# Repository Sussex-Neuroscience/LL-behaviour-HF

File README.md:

# LL-behaviour-HF

a behavioural control system for head fixed mice

The task:

- At the start there is a 10 sec interval without a stimulus to record baseline activity. Then the mouse sees a stimulus (always the same drifting grating) which appears randomly either on the left or the right screen. after 5 sec. of stimulus presentation the actuator moves the lick sensors in front of the mouse for two sec. in which the mouse has to report on which side the stimulus is present, hence lick left or right. If the answer is correct a reward is given (solenoid valves). If the answer is incorrect no reward is given. The actuator retracts the lick sensors after 2 sec. either way. Then there is an inter trial interval for 5+ sec before the next stimulus will be presented. If the mouse was incorrect the stimulus will be presented on the same side as the trial before until the mouse makes the correct decision (to avoid bias).I might want to change the timeframes for the different stages depending on how the training goes.

- There will also be a second task where stimuli are presented on both sides on the screen (differing in orientation or contrast) and the animal has to decide which of the stimuli is the correct one. The time course will be the same, it is just the task that is changing.

- The stimulus orientation, size, contrast, frequencies etc. will be different for every mouse but will be the same throughout the training sessions, so there is only 1 type of stimulus in the first task and 2 type of stimuli in the second task. 

- The random stimulus presentation isn't in the code yet. So far, there was no task for the animal, so we always displayed the same stimulus on both sides simultaneously by mirroring one screen to the other. I'll have another chat with Antonio today to see how trivial it is to change that towards what I need.

- As for the scanimage channels. Yes, I was talking about the analog inputs. The DAQ has a lot of free slots left and I guess there are free digital inputs. I'm not too familiar with setting these things up.

- If everything works just using the labjack that would be great. We have an Arduino uno lying around just in case it is needed.

---

schematics on how the system is working and how it should work:

--- 

### notes on implementation:

from what I could gather, Psychopy is not indicated to do millisecond precision of many different variables at once. I had a look on how it deals with timing (more info [here](https://www.psychopy.org/_modules/psychopy/clock.html#Clock)), and thinking that a good route would be to do the behavioural timing critical things on the ESP32.

---

initial bill of materials:

|||
|---|---|
|Linear actuator||
|solenoid valves||
|lick sensors||
|beehive main board||
|beehive peltier board||
|beehive solenoid valve board||
|||

---

software needed to run the esp32
REPL
esp32 micropython firmware
adafruit Ampy

---

notes from the first installation session:

- the Optogenetics LED is controlled by a Thorlabs DC2200 interface. It gets its signals from an arduino box, which in principle can be bypassed since we are already using a microcontroller to take care of the behavioural task.
- from labjack to scanimage there are 2 signals timewave and twoptrigger.

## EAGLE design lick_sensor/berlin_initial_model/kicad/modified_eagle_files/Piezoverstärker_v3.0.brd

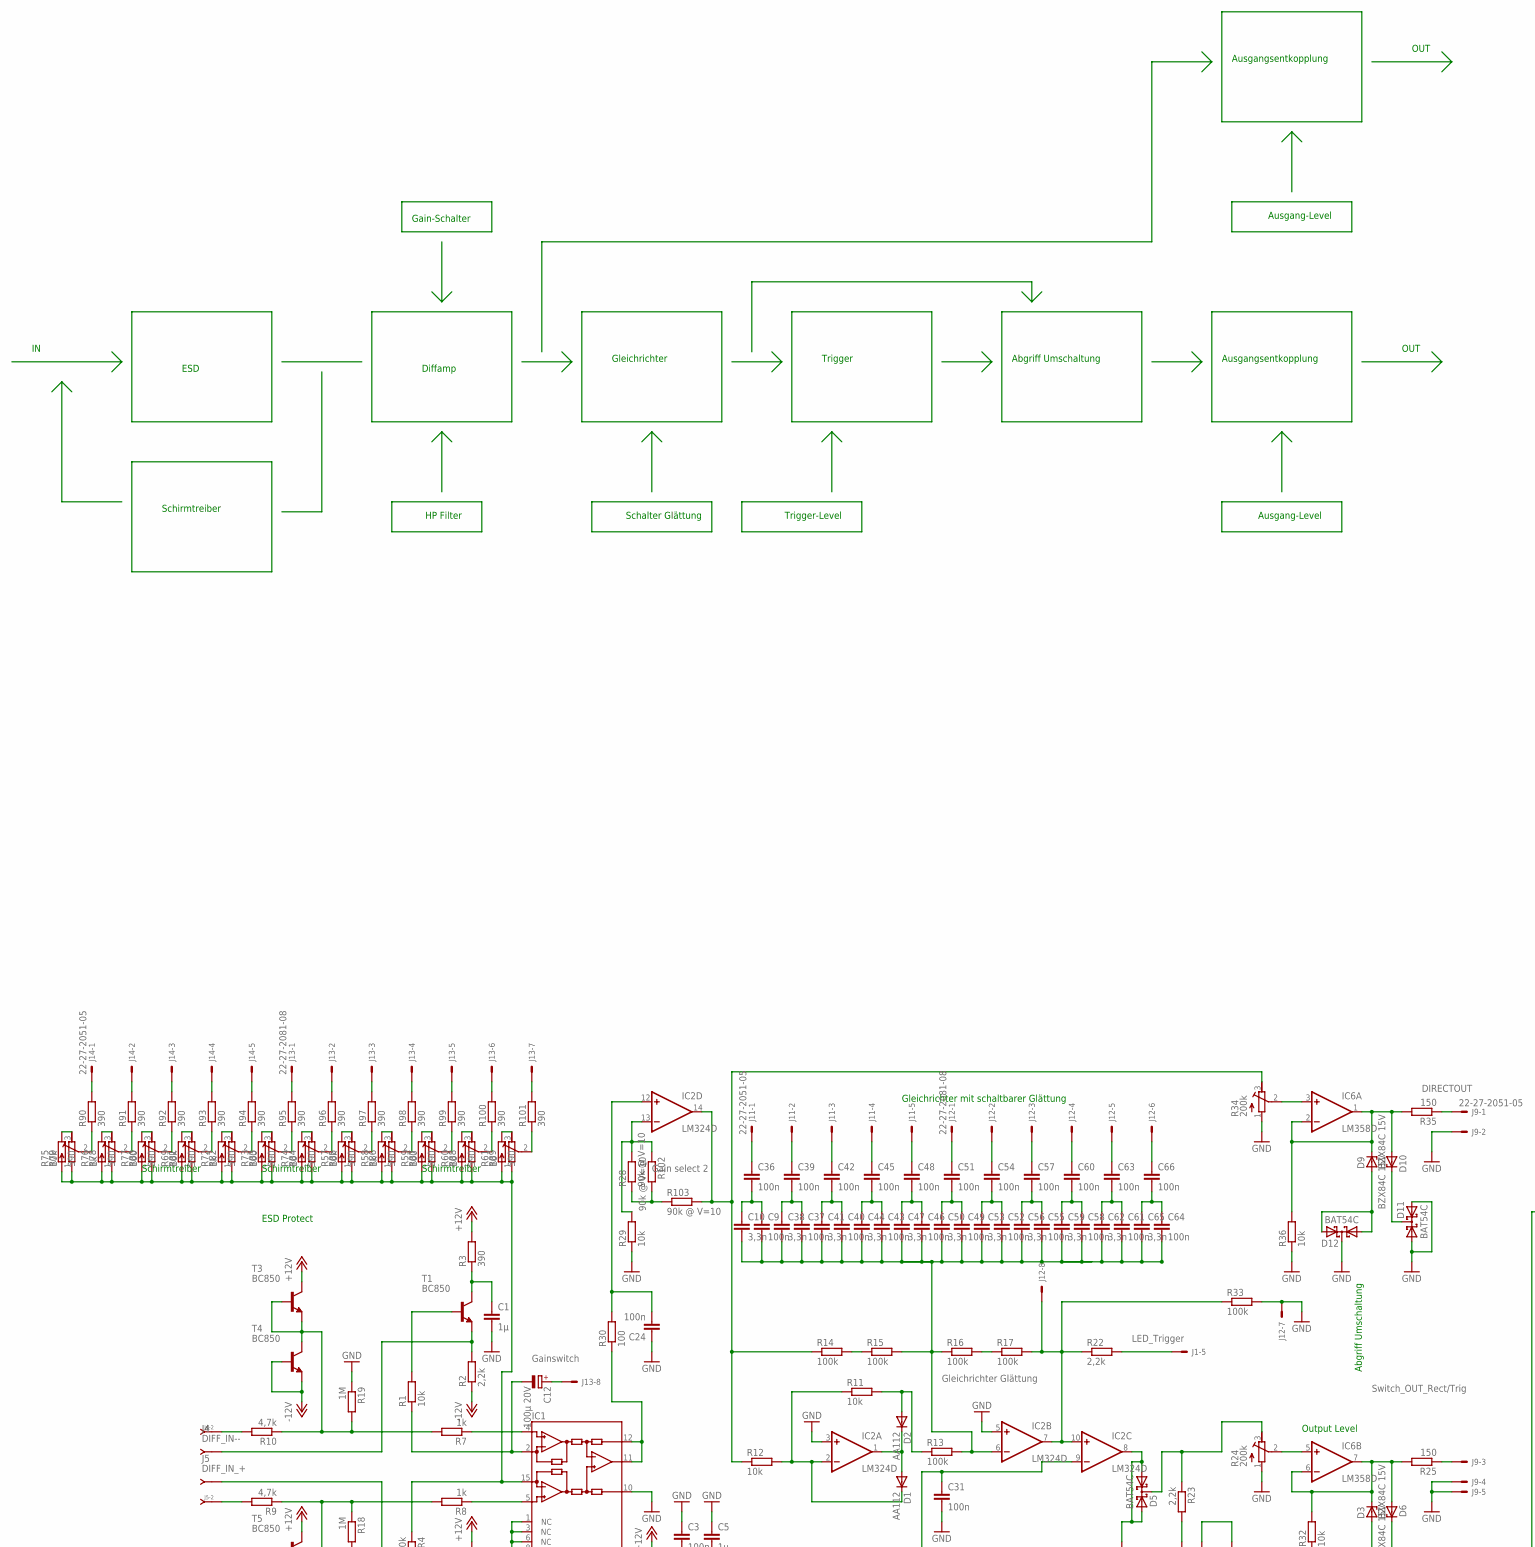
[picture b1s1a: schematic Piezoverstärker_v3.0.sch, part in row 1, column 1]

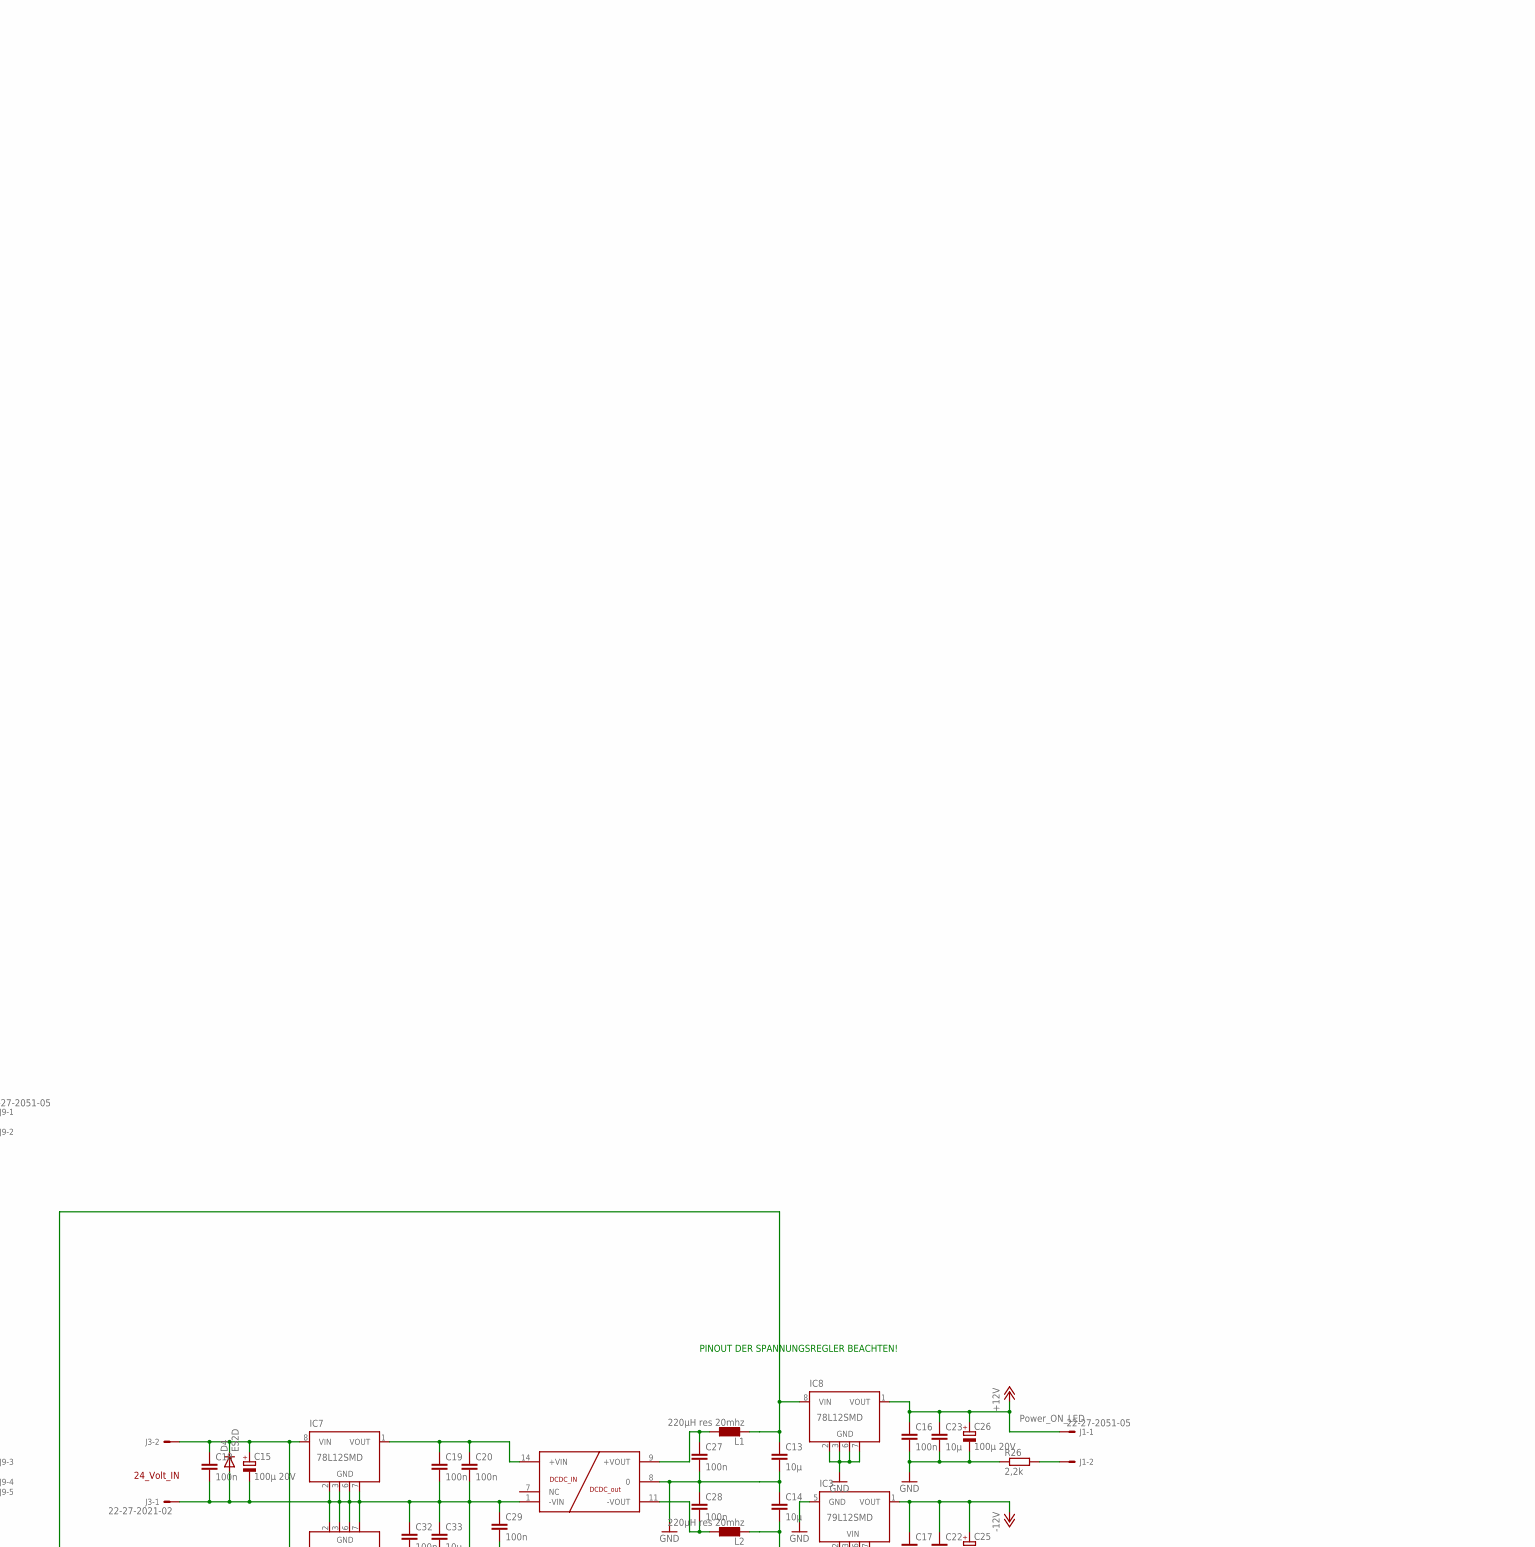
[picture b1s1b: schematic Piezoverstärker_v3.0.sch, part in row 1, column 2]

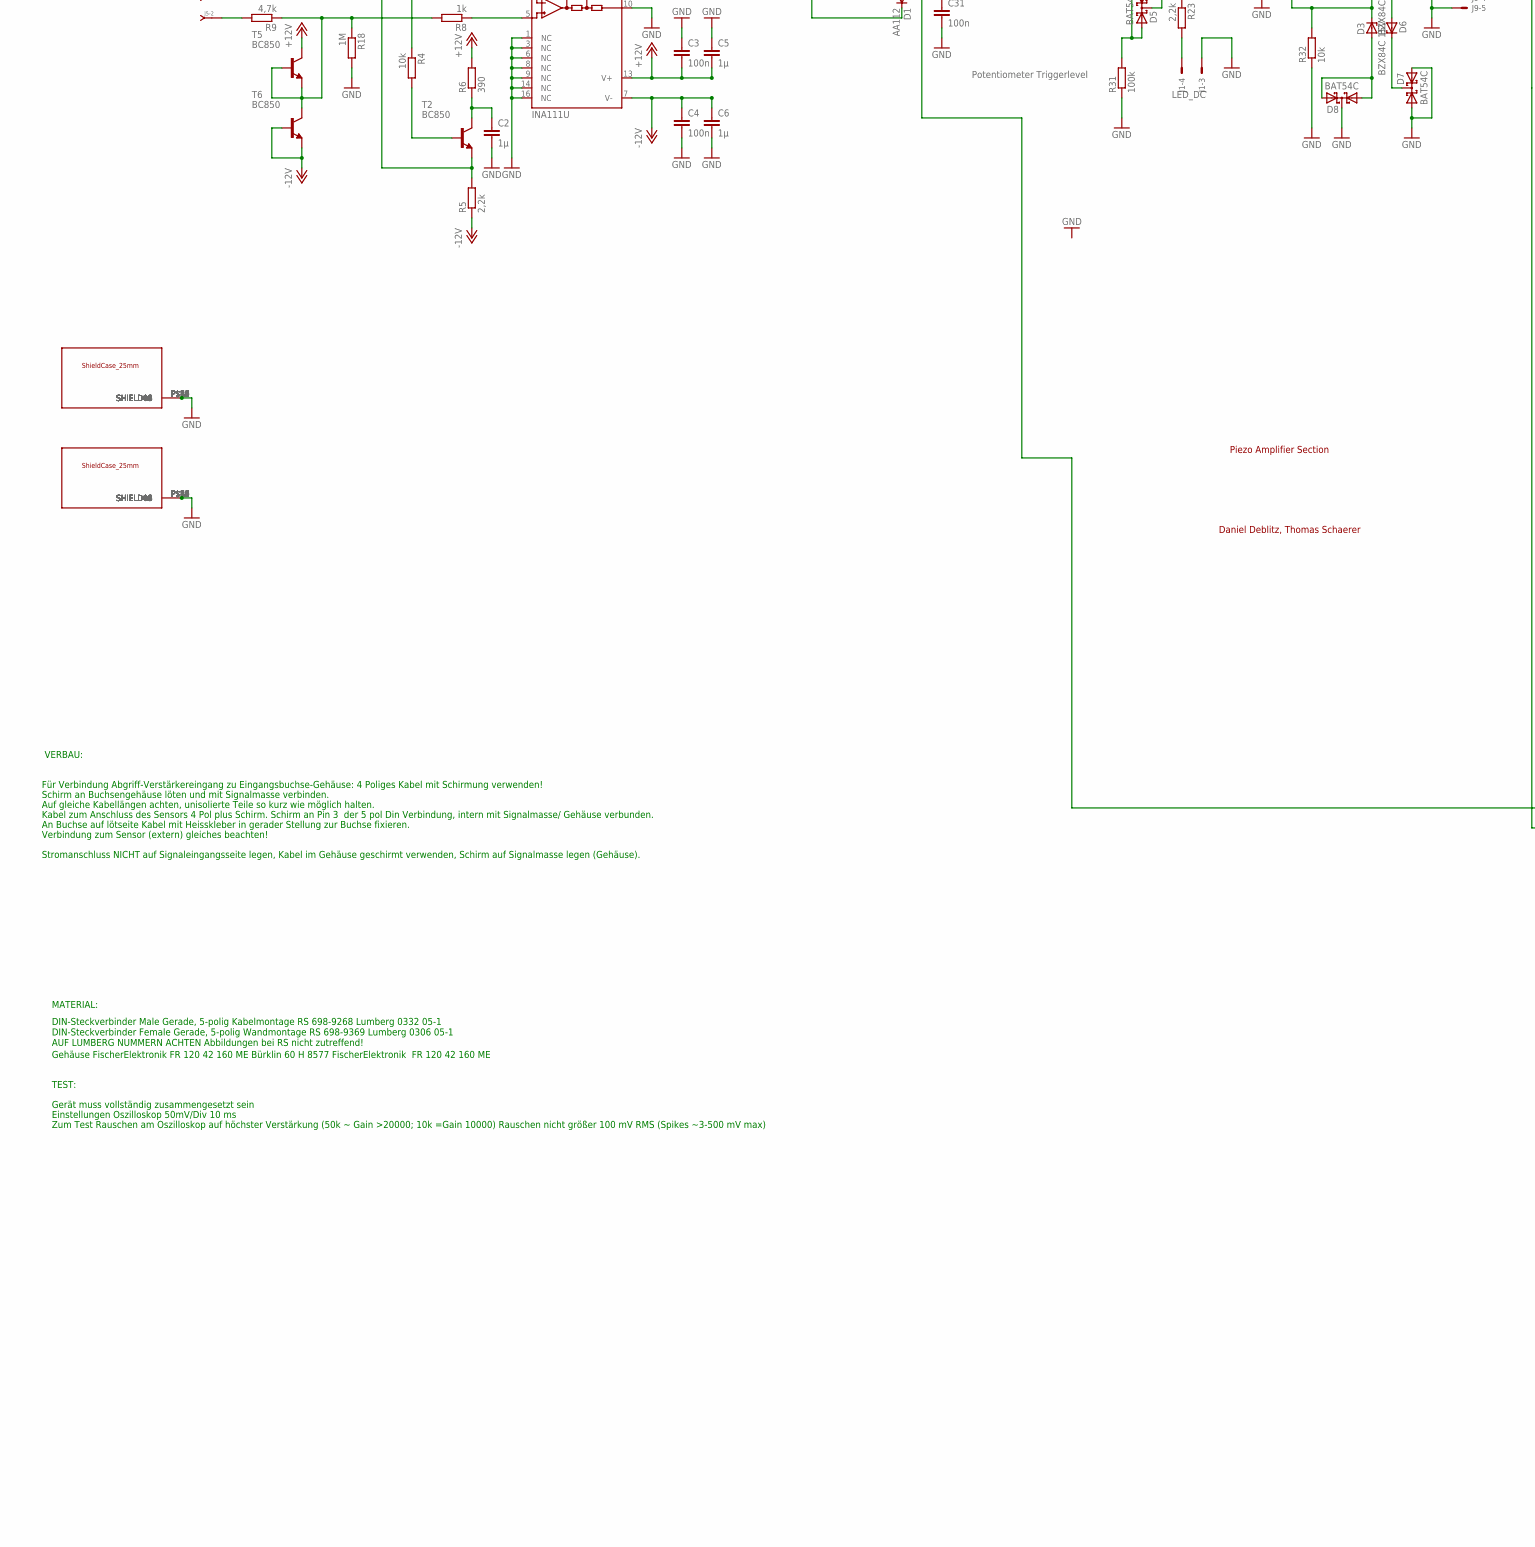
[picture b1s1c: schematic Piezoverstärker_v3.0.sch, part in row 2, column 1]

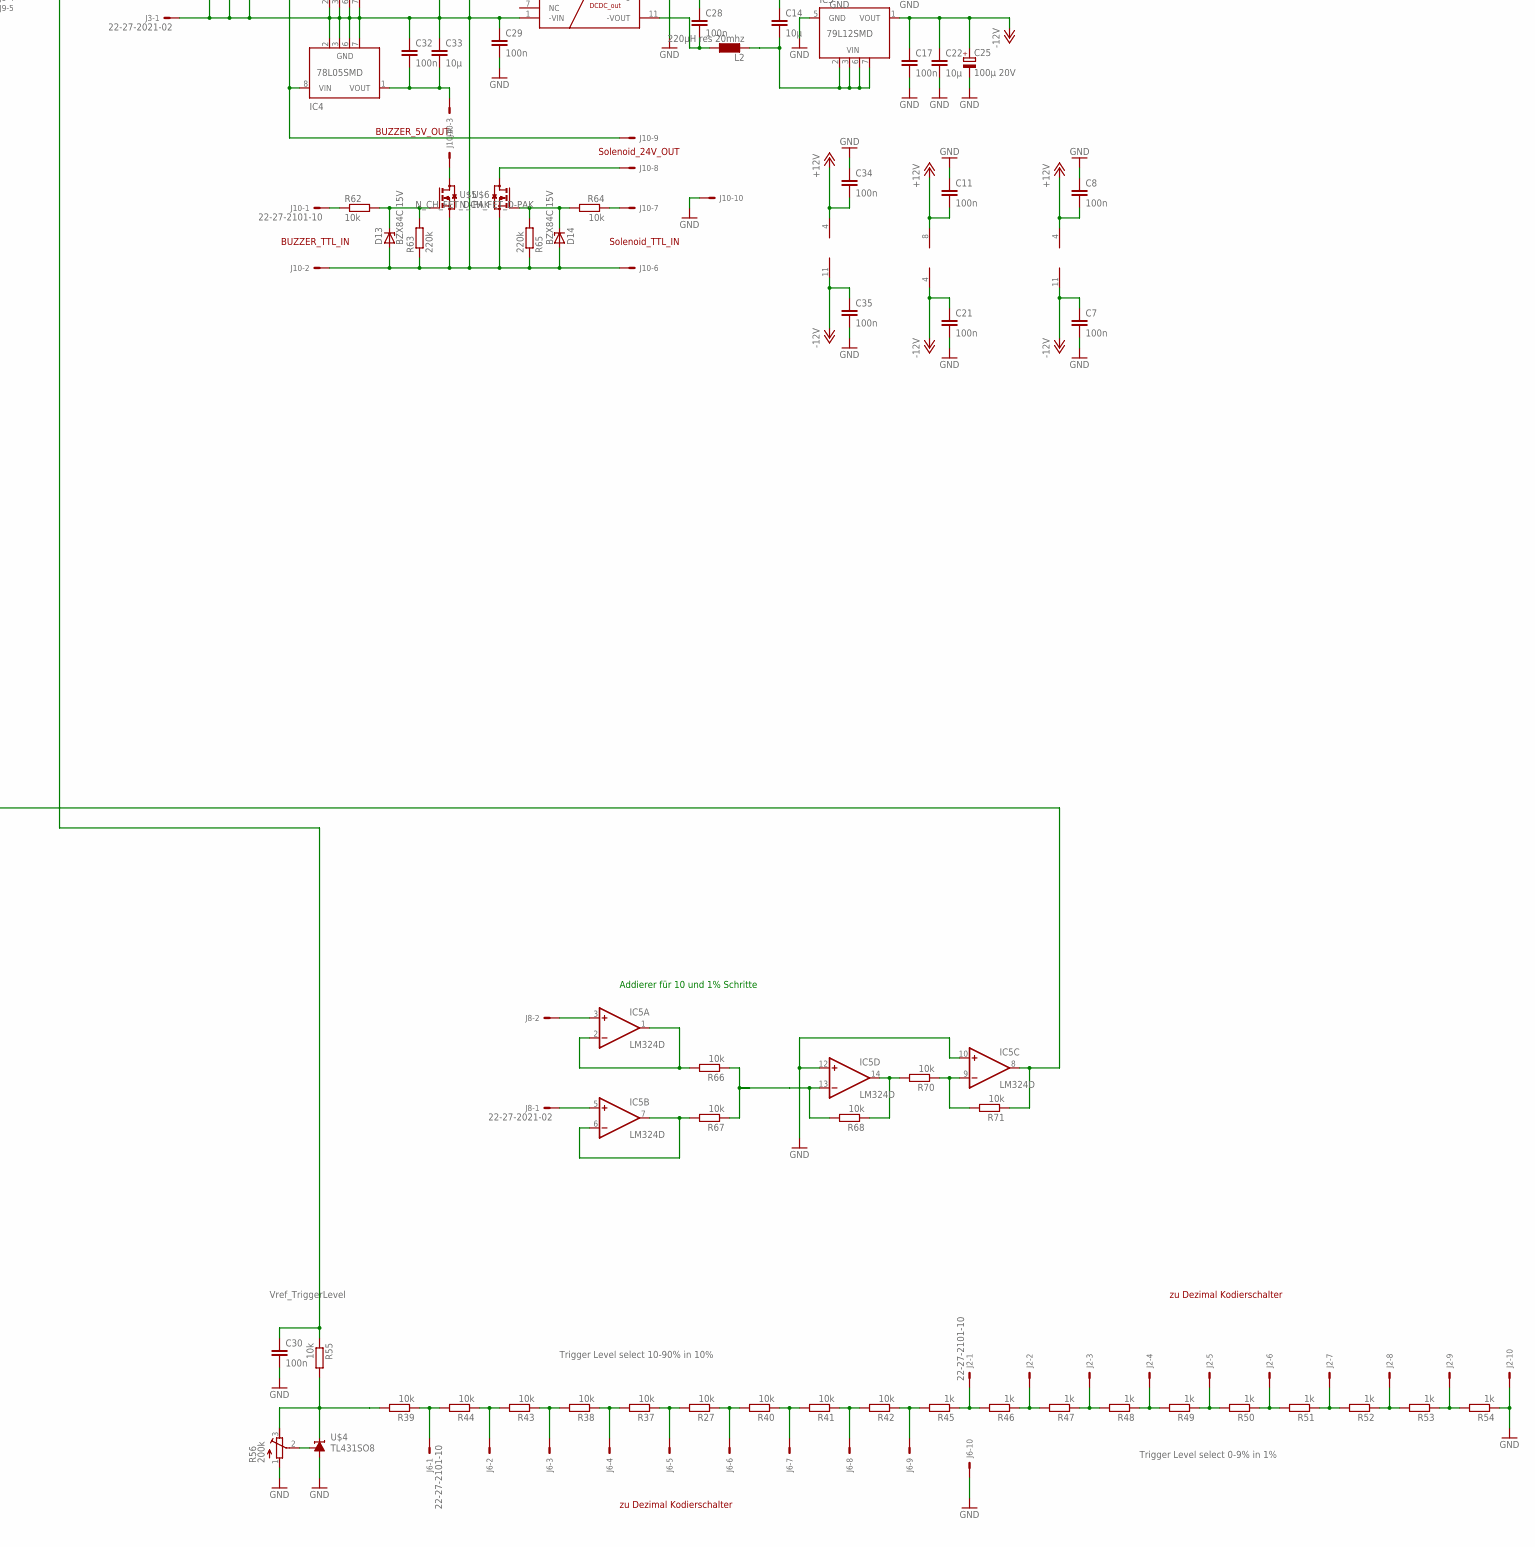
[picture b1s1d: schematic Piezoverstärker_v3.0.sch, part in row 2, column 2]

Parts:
C1, C2, C5, C6: 1µ; C0805
C3, C4, C7, C8, C9, C11, C16, C17, C18, C19, C20, C21, C24, C27, C28, C29, C30, C31, C32, C34, C35, C36, C37, C39, C40, C42, C43, C45, C46, C48, C49, C51, C52, C54, C55, C57, C58, C60, C61, C63, C64, C66: 100n; C0805
C10, C38, C41, C44, C47, C50, C53, C56, C59, C62, C65: 3,3n; C0805
C12, C15, C25, C26: 100µ 20V; PANASONIC_E
C13, C14, C22, C23, C33: 10µ; C0805
D1, D2: AA112; DO07
D3, D6, D9, D10, D13, D14: BZX84C 15V; TO236
D4: ES2D; SMB
D5, D7, D8, D11, D12: BAT54C; SOT23
IC1: INA111U; SO16-1
IC2, IC5: LM324D; SO14
IC3: 79L12SMD; SO08
IC4: 78L05SMD; SO08
IC6: LM358D; SO08
IC7, IC8: 78L12SMD; SO08
J1, J9, J11, J14: 22-27-2051-05; 6410-05
J2, J6, J10: 22-27-2101-10; 6410-10
J3, J8: 22-27-2021-02; 6410-02
J4: DIFF_IN--; SIP-100-02-40
J5: DIFF_IN_+; SIP-100-02-40
J12, J13: 22-27-2081-08; 6410-08
L1, L2: 220µH res 20mhz; L4532P
R1, R4, R11, R12, R27, R29, R32, R36, R37, R38, R39, R40, R41, R42, R43, R44, R55, R62, R64, R66, R67, R68, R70, R71: 10k; R0805
R2, R5, R22, R23, R26: 2,2k; R0805
R3, R6, R78, R79, R80, R81, R82, R83, R84, R85, R86, R87, R88, R89, R90, R91, R92, R93, R94, R95, R96, R97, R98, R99, R100, R101: 390; R0805
R7, R8, R45, R46, R47, R48, R49, R50, R51, R52, R53, R54: 1k; R0805
R9, R10: 4,7k; R0805
R13, R14, R15, R16, R17, R31, R33: 100k; R0805
R18, R19: 1M; R0805
R24, R34, R56: 200k; RTRIM74W
R25, R35: 150; R0805
R28, R102, R103: 90k @ V=10; R0805
R30: 100; R0805
R57, R69, R75: 10k; RTRIM74W
R58, R72, R76: 1k; RTRIM74W
R59, R73, R77: 100; RTRIM74W
R60, R61, R74: 10; RTRIM74W
R63, R65: 220k; R0805
T1, T2, T3, T4, T5, T6: BC850; SOT23
U$1: MURATA_DCDC_NMA1215DC; MURRATA_NMA_DCDC
U$2, U$3: ABSCHIRMGEHäUSE_SMD_25MM
U$4: TL431SO8; SO08
U$5, U$6: N_CH_FET_D-PAK; TO252

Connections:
+12V: C3.2, C5.2, C8.2, C11.2, C16.1, C23.1, C26.+, C34.2, IC1.13 (V+), IC2.4 (V+), IC5.4 (V+), IC6.8 (V+), IC8.1 (VOUT), J1.1, R3.2, R6.2, T3.3 (C), T5.3 (C)
+12VDC_DIRTY: C13.1, C30.1, IC8.8 (VIN), L1.2, R55.1
-12V: C4.1, C6.1, C7.1, C17.1, C21.1, C22.1, C25.+, C35.1, IC1.7 (V-), IC2.11 (V-), IC3.1 (VOUT), IC5.11 (V-), IC6.4 (V-), R2.1, R5.1, T4.1 (B), T4.2 (E), T6.1 (B), T6.2 (E)
DIFF_+: R8.2, R9.1, R18.1, T5.1 (B), T5.2 (E), T6.3 (C)
DIFF_-: R7.2, R10.1, R19.2, T3.1 (B), T3.2 (E), T4.3 (C)
GND: C1.2, C2.2, C3.1, C4.2, C5.1, C6.2, C7.2, C8.1, C11.1, C13.2, C14.1, C16.2, C17.2, C21.2, C22.2, C23.2, C24.1, C25.-, C26.-, C27.2, C28.1, C29.2, C30.2, C31.2, C34.1, C35.2, D7.1 (A1), D7.2 (A2), D8.3 (CC), D11.1 (A1), D11.2 (A2), D12.3 (CC), IC1.1 (NC), IC1.3 (NC), IC1.6 (NC), IC1.8 (NC), IC1.9 (NC), IC1.10 (REF), IC1.14 (NC), IC1.16 (NC), IC2.3 (+IN), IC2.5 (+IN), IC3.5 (GND), IC5.10 (+IN), IC5.12 (+IN), IC8.2 (GND), IC8.3 (GND), IC8.6 (GND), IC8.7 (GND), J1.3, J2.10, J6.10, J9.2, J9.4, J9.5, J10.10, J12.7, R18.2, R19.1, R24.1 (E), R26.1, R29.1, R31.1, R32.1, R33.2, R34.1 (E), R36.1, R54.1, R56.1 (E), U$1.8 (0), U$2.P$1 (SHIELD00), U$2.P$2 (SHIELD01), U$2.P$3 (SHIELD02), U$2.P$4 (SHIELD03), U$2.P$5 (SHIELD04), U$2.P$6 (SHIELD05), U$2.P$7 (SHIELD06), U$2.P$8 (SHIELD07), U$2.P$9 (SHIELD08), U$2.P$10 (SHIELD09), U$2.P$11 (SHIELD10), U$2.P$12 (SHIELD11), U$2.P$13 (SHIELD12), U$2.P$14 (SHIELD13), U$2.P$15 (SHIELD14), U$2.P$16 (SHIELD15), U$2.P$17 (SHIELD16), U$2.P$18 (SHIELD17), U$2.P$19 (SHIELD18), U$2.P$20 (SHIELD19), U$3.P$1 (SHIELD00), U$3.P$2 (SHIELD01), U$3.P$3 (SHIELD02), U$3.P$4 (SHIELD03), U$3.P$5 (SHIELD04), U$3.P$6 (SHIELD05), U$3.P$7 (SHIELD06), U$3.P$8 (SHIELD07), U$3.P$9 (SHIELD08), U$3.P$10 (SHIELD09), U$3.P$11 (SHIELD10), U$3.P$12 (SHIELD11), U$3.P$13 (SHIELD12), U$3.P$14 (SHIELD13), U$3.P$15 (SHIELD14), U$3.P$16 (SHIELD15), U$3.P$17 (SHIELD16), U$3.P$18 (SHIELD17), U$3.P$19 (SHIELD18), U$3.P$20 (SHIELD19), U$4.2 (A)
unnamed: C1.1, R3.1, T1.3 (C)
unnamed: IC1.11 (OUT), IC1.12 (FB), R30.1
unnamed: R1.2, T1.1 (B)
unnamed: C12.-, IC1.2 (RG), R1.1
unnamed: C2.1, R6.1, T2.3 (C)
unnamed: IC1.5 (+IN), R8.1
unnamed: R4.2, T2.1 (B)
unnamed: R75.2 (S), R90.1
unnamed: IC1.4 (-IN), R7.1
unnamed: R75.3 (A), R79.2
unnamed: J4.2, R10.2
unnamed: J5.2, R9.2
unnamed: IC6.5 (+IN), R24.2 (S)
unnamed: C12.+, J13.8
unnamed: D1.A, D2.C, IC2.1 (OUT)
unnamed: D5.1 (A1), D5.2 (A2), IC2.8 (OUT), R31.2
unnamed: D2.A, R11.2, R13.1
unnamed: J9.3, R25.1
unnamed: C28.2, L2.1, U$1.11 (-VOUT)
unnamed: R14.2, R15.1
unnamed: R16.2, R17.1
unnamed: IC2.7 (OUT), IC2.10 (+IN), J12.8, R17.2, R22.1, R33.1
unnamed: C9.2, C10.2, C37.2, C38.2, C40.2, C41.2, C43.2, C44.2, C46.2, C47.2, C49.2, C50.2, C52.2, C53.2, C55.2, C56.2, C58.2, C59.2, C61.2, C62.2, C64.2, C65.2, IC2.6 (-IN), R13.2, R15.2, R16.1
unnamed: C9.1, C10.1, C36.2
unnamed: C45.1, J11.4
unnamed: C37.1, C38.1, C39.2
unnamed: R76.3 (A), R78.2
unnamed: R77.3 (A), R80.2
unnamed: J1.5, R22.2
unnamed: J1.4, R23.2
unnamed: R39.2, R55.2, R56.3 (A), U$4.1 (C)
unnamed: D5.3 (CC), R23.1, R24.3 (A)
unnamed: D3.A, D8.1 (A1), D8.2 (A2)
unnamed: D3.C, D6.A, IC6.6 (-IN), IC6.7 (OUT), R25.2, R32.2
unnamed: C27.1, L1.1, U$1.9 (+VOUT)
unnamed: J2.9, R53.1, R54.2
unnamed: C15.+, C18.1, D4.C, IC4.8 (VIN), IC7.8 (VIN), J3.2, J10.9
unnamed: C19.1, C20.1, IC7.1 (VOUT), U$1.14 (+VIN)
unnamed: D1.C, IC2.2 (-IN), R11.1, R12.2
unnamed: D6.C, D7.3 (CC)
unnamed: D9.C, D10.A, IC6.1 (OUT), IC6.2 (-IN), R35.2, R36.2
unnamed: IC6.3 (+IN), R34.2 (S)
unnamed: J9.1, R35.1
unnamed: J1.2, R26.2
unnamed: D9.A, D12.1 (A1), D12.2 (A2)
unnamed: D10.C, D11.3 (CC)
unnamed: IC2.13 (-IN), R28.2, R29.2, R102.1
unnamed: C42.1, J11.3
unnamed: IC2.14 (OUT), R12.1, R14.1, R34.3 (A), R103.2
unnamed: J2.8, R52.1, R53.2
unnamed: C24.2, IC2.12 (+IN), R30.2
unnamed: J2.7, R51.1, R52.2
unnamed: J2.6, R50.1, R51.2
unnamed: J2.5, R49.1, R50.2
unnamed: J2.4, R48.1, R49.2
unnamed: J2.3, R47.1, R48.2
unnamed: J2.2, R46.1, R47.2
unnamed: J2.1, R45.1, R46.2
unnamed: J6.9, R42.1, R45.2
unnamed: J6.8, R41.1, R42.2
unnamed: J6.7, R40.1, R41.2
unnamed: J6.6, R27.1, R40.2
unnamed: J6.5, R27.2, R37.1
unnamed: J6.4, R37.2, R38.1
unnamed: J6.3, R38.2, R43.1
unnamed: J6.2, R43.2, R44.1
unnamed: J6.1, R39.1, R44.2
unnamed: R56.2 (S), U$4.8 (FB)
unnamed: C40.1, C41.1, C42.2
unnamed: C39.1, J11.2
unnamed: C43.1, C44.1, C45.2
unnamed: C36.1, J11.1
unnamed: IC1.15 (RG), R4.1, R57.1 (E), R58.1 (E), R59.1 (E), R60.1 (E), R61.1 (E), R69.1 (E), R72.1 (E), R73.1 (E), R74.1 (E), R75.1 (E), R76.1 (E), R77.1 (E), R78.1, R79.1, R80.1, R81.1, R82.1, R83.1, R84.1, R85.1, R86.1, R87.1, R88.1, R89.1
unnamed: C32.2, C33.2, IC4.1 (VOUT), J10.3
unnamed: J10.4, U$5.3 (D)
unnamed: J10.1, R62.1
unnamed: D13.C, R62.2, R63.2, U$5.1 (G)
unnamed: J10.8, U$6.3 (D)
unnamed: J10.7, R64.1
unnamed: D14.C, R64.2, R65.2, U$6.1 (G)
unnamed: IC5.6 (-IN), IC5.7 (OUT), R67.2
unnamed: IC5.1 (OUT), IC5.2 (-IN), R66.2
unnamed: IC5.5 (+IN), J8.1
unnamed: IC5.3 (+IN), J8.2
unnamed: C46.1, C47.1, C48.2
unnamed: IC5.13 (-IN), R66.1, R67.1, R68.2
unnamed: IC5.14 (OUT), R68.1, R70.2
unnamed: IC5.9 (-IN), R70.1, R71.2
unnamed: C48.1, J11.5
unnamed: C49.1, C50.1, C51.2
unnamed: C51.1, J12.1
unnamed: C52.1, C53.1, C54.2
unnamed: C54.1, J12.2
unnamed: C55.1, C56.1, C57.2
unnamed: C57.1, J12.3
unnamed: C58.1, C59.1, C60.2
unnamed: C60.1, J12.4
unnamed: C61.1, C62.1, C63.2
unnamed: C63.1, J12.5
unnamed: C64.1, C65.1, C66.2
unnamed: C66.1, J12.6
unnamed: R76.2 (S), R91.1
unnamed: R77.2 (S), R92.1
unnamed: R69.2 (S), R93.1
unnamed: R72.2 (S), R94.1
unnamed: R73.2 (S), R95.1
unnamed: R74.2 (S), R96.1
unnamed: R57.2 (S), R97.1
unnamed: R58.2 (S), R98.1
unnamed: R59.2 (S), R99.1
unnamed: R60.2 (S), R100.1
unnamed: R61.2 (S), R101.1
unnamed: J14.1, R90.2
unnamed: J14.2, R91.2
unnamed: J14.3, R92.2
unnamed: J14.4, R93.2
unnamed: J14.5, R94.2
unnamed: J13.1, R95.2
unnamed: J13.2, R96.2
unnamed: J13.3, R97.2
unnamed: J13.4, R98.2
unnamed: J13.5, R99.2
unnamed: J13.6, R100.2
unnamed: J13.7, R101.2
unnamed: R28.1, R102.2, R103.1
unnamed: R69.3 (A), R81.2
unnamed: R72.3 (A), R82.2
unnamed: R73.3 (A), R83.2
unnamed: R74.3 (A), R84.2
unnamed: R57.3 (A), R85.2
unnamed: R58.3 (A), R86.2
unnamed: R59.3 (A), R87.2
unnamed: R60.3 (A), R88.2
unnamed: R61.3 (A), R89.2
SCHIR_DIFF_+: J5.1, R5.2, T2.2 (E)
SCHIR_DIFF_-: J4.1, R2.2, T1.2 (E)
T1: C15.-, C18.2, C19.2, C20.2, C29.1, C32.1, C33.1, D4.A, D13.A, D14.A, IC4.2 (GND), IC4.3 (GND), IC4.6 (GND), IC4.7 (GND), IC7.2 (GND), IC7.3 (GND), IC7.6 (GND), IC7.7 (GND), J3.1, J10.2, J10.6, R63.1, R65.1, U$1.1 (-VIN), U$5.2 (S), U$6.2 (S)
T2: C14.2, IC3.2 (VIN), IC3.3 (VIN), IC3.6 (VIN), IC3.7 (VIN), L2.2
TRIGGER_LEVELSET_IN: C31.1, IC2.9 (-IN), IC5.8 (OUT), R71.1

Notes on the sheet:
Gleichrichter mit schaltbarer Glättung
ESD Protect
Schirmtreiber
Potentiometer Triggerlevel
Output Level
Gainswitch
ESD
Diffamp
Gain-Schalter
Gleichrichter
Trigger
Abgriff Umschaltung
HP Filter
Schalter Glättung
Trigger-Level
Ausgangsentkopplung
Ausgang-Level
OUT
PINOUT DER SPANNUNGSREGLER BEACHTEN!
Zum Test Rauschen am Oszilloskop auf höchster Verstärkung (50k ~ Gain >20000; 10k =Gain 10000) Rauschen nicht größer 100 mV RMS (Spikes ~3-500 mV max)
Gerät muss vollständig zusammengesetzt sein
Für Verbindung Abgriff-Verstärkereingang zu Eingangsbuchse-Gehäuse: 4 Poliges Kabel mit Schirmung verwenden!
Kabel zum Anschluss des Sensors 4 Pol plus Schirm. Schirm an Pin 3 der 5 pol Din Verbindung, intern mit Signalmasse/ Gehäuse verbunden.
Einstellungen Oszilloskop 50mV/Div 10 ms
Auf gleiche Kabellängen achten, unisolierte Teile so kurz wie möglich halten.
An Buchse auf lötseite Kabel mit Heisskleber in gerader Stellung zur Buchse fixieren.
TEST:
MATERIAL:
Schirm an Buchsengehäuse löten und mit Signalmasse verbinden.
Verbindung zum Sensor (extern) gleiches beachten!
DIN-Steckverbinder Male Gerade, 5-polig Kabelmontage RS 698-9268 Lumberg 0332 05-1 DIN-Steckverbinder Female Gerade, 5-polig Wandmontage RS 698-9369 Lumberg 0306 05-1 AUF LUMBERG NUMMERN ACHTEN Abbildungen bei RS nicht zutreffend!
VERBAU:
Gehäuse FischerElektronik FR 120 42 160 ME Bürklin 60 H 8577 FischerElektronik FR 120 42 160 ME
Stromanschluss NICHT auf Signaleingangsseite legen, Kabel im Gehäuse geschirmt verwenden, Schirm auf Signalmasse legen (Gehäuse).
Gleichrichter Glättung
LED_Trigger
LED_DC
Switch_OUT_Rect/Trig
Power_ON_LED
Gain select 2

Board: 2 copper layers, 216 parts (0 on the bottom side), 145 nets, no tracks yet.

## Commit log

2021-04-08 initial update of information
2021-04-08 initial org of files
2021-04-08 first pass at task1
2021-04-14 work on micropython code, suggestions to python code that runs on computer and update ot readme
2021-04-28 change how timing is controlled (everything controlled by the microcontroller, add .vscode to gitignore, reorganize the repo)
2021-05-10 work on code and list of materials
2021-05-17 start building licksensors fit
2021-05-19 changes to designs
2021-05-24 work on code
2021-05-24 add more code
2021-05-24 add tests
2021-05-26 code update and tests
2021-05-27 work on tests and 3D printed parts
2021-05-28 solved solenoid bugs
2021-06-01 update host code and task code
2021-06-04 fix bugs, update code
2021-06-07 update host and microcontroller code
2021-06-15 add code to create CSV file containing monitor side and code to update EEPROM on DAC board
2021-07-07 last changes leading to 1st working version on setup
2021-08-07 update code so that lick responses are registered on DAC
2021-08-18 add Sina's ppt with the task schematic and photos, as well as update code to print correct/incorrect trial numbers
2021-08-20 add some minor changes to code
2021-10-22 start working on the servo implementation
2021-10-28 work on new movement system for spouts
2021-11-02 more work on servo fit
2021-11-03 add sensor holder
2021-11-10 update code and models for servo actuator
2021-12-07 update python conde and clean up repo
2021-12-10 clean up repo
2021-12-10 clean up repo and create code to upload files to micropython board via notebook
2021-12-13 implement a not so good way to save files on host computer
2022-01-13 update code and jupyter notebooks
2022-02-18 update templates
2022-02-18 add training with constant wop
2022-08-23 split 3D models into useable individual parts
2022-10-21 update 3D models for the piezo holder

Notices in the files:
parts and their libraries:
con-headers-jp: Copyright (C) 2008, Bob Starr
